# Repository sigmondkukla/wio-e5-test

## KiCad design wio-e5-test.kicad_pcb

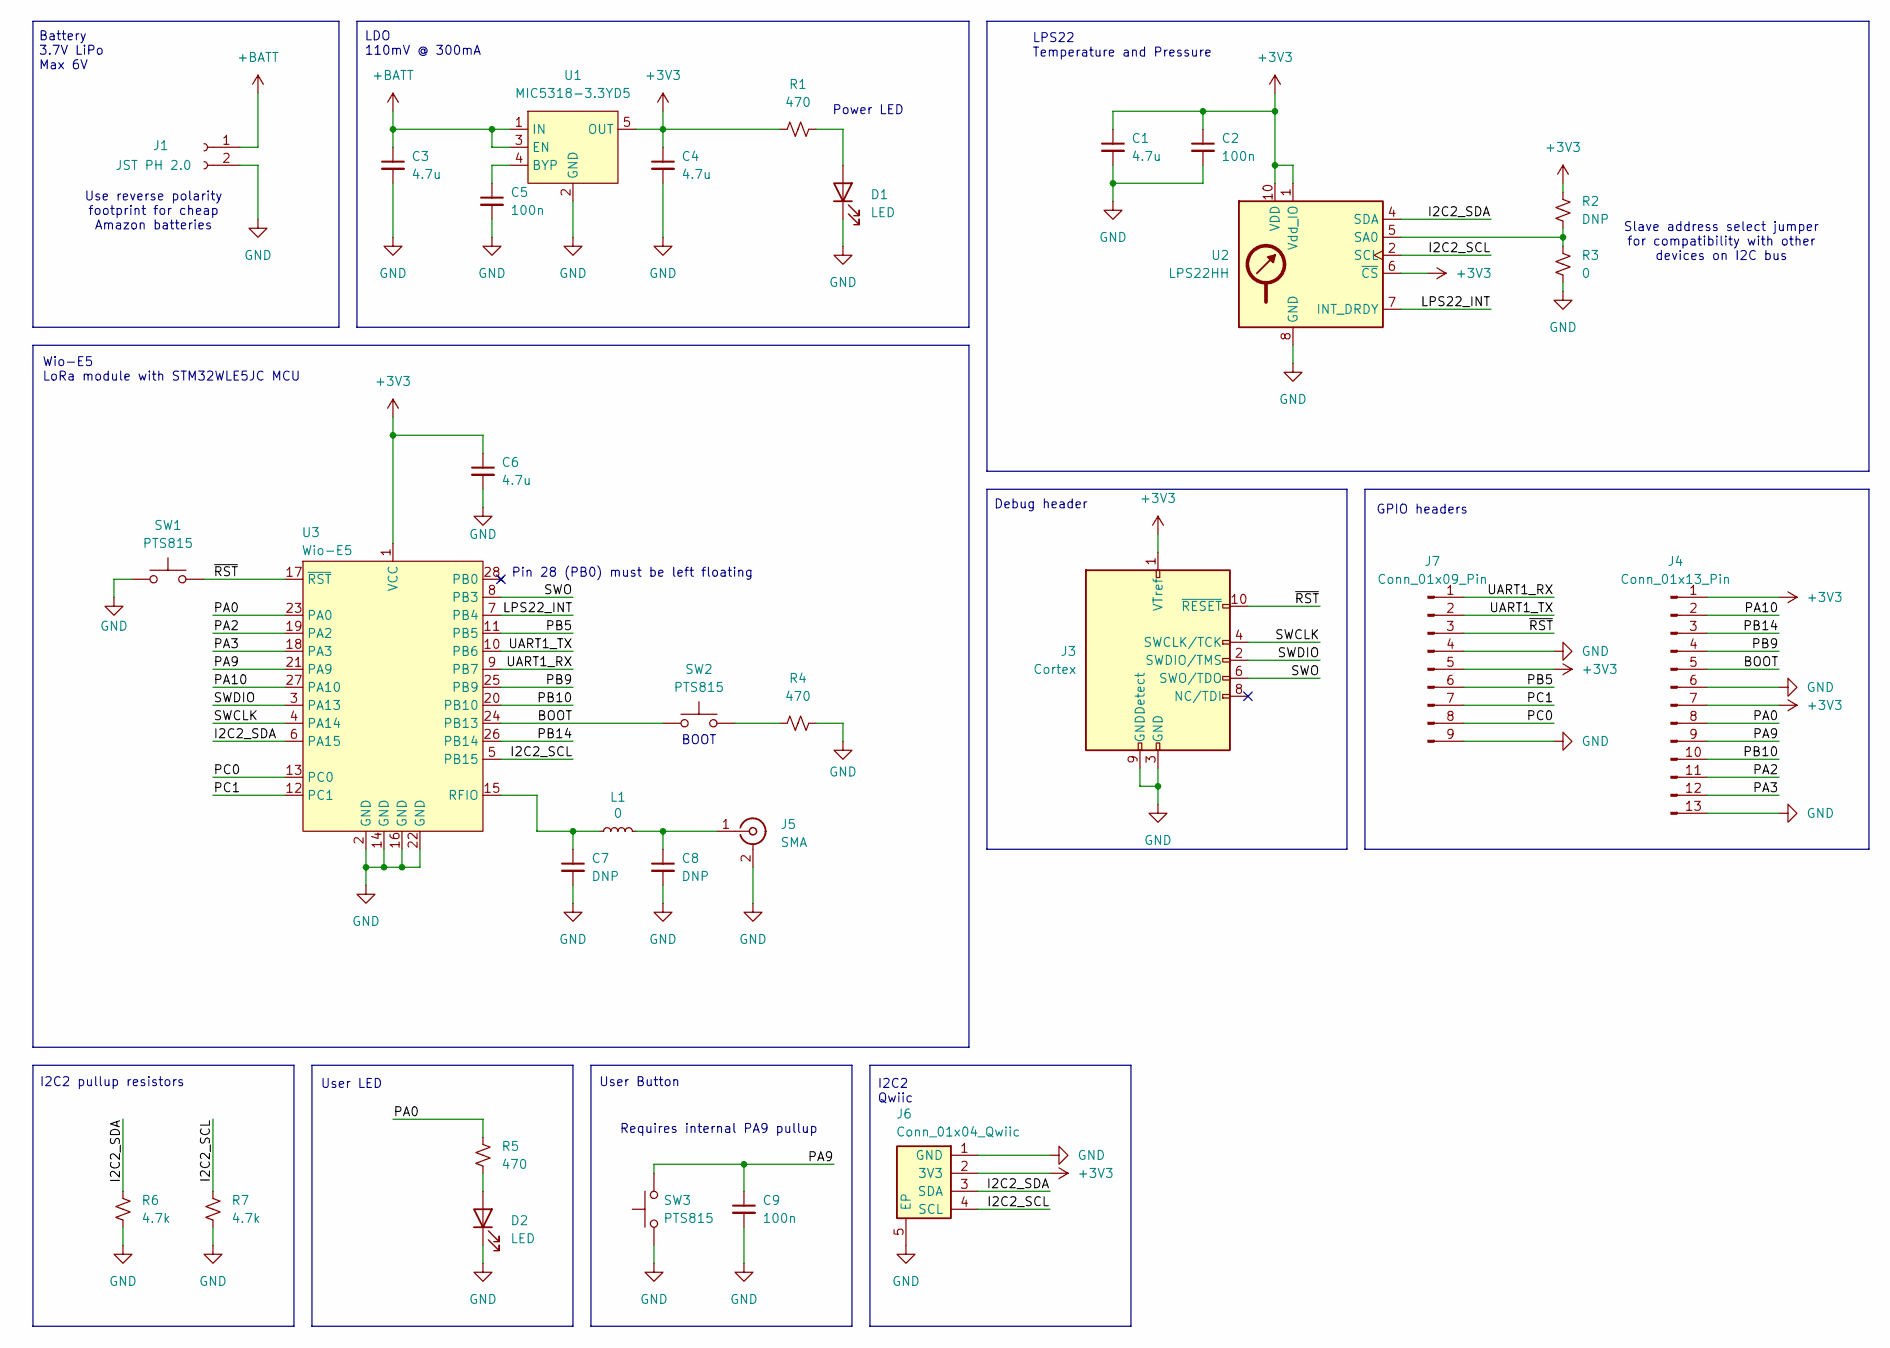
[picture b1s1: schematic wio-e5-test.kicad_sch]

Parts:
C1, C3, C4, C6: 4.7u; C_0603_1608Metric
C2, C5, C9: 100n; C_0603_1608Metric
C7, C8: DNP; C_0603_1608Metric
D1, D2: LED; LED_0603_1608Metric
J1: JST PH 2.0; JST_PH_S2B-PH-K_1x02_P2.00mm_Horizontal
J3: Cortex; CONN_3220-10-0100-00_CNC
J4: Conn_01x13_Pin; PinHeader_1x13_P2.54mm_Vertical
J5: SMA; SMA_Samtec_SMA-J-P-H-ST-EM1_EdgeMount
J6: Conn_01x04_Qwiic; CONN_JST-BM04B-SRSS-TB
J7: Conn_01x09_Pin; PinHeader_1x09_P2.54mm_Vertical
L1: 0; L_0603_1608Metric
R1, R4, R5: 470; R_0603_1608Metric
R2: DNP; R_0603_1608Metric
R3: 0; R_0603_1608Metric
R6, R7: 4.7k; R_0603_1608Metric
SW1, SW2, SW3: PTS815; SW_Push_PTS815_SJM_250_SMTR_LFS
U1: MIC5318-3.3YD5; SOT-23-5
U2: LPS22HH; ST_HLGA-10_2x2mm_P0.5mm_LayoutBorder3x2y
U3: Wio-E5

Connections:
+3V3: C1.1, C2.1, C4.1, C6.1, J3.1 (VTref), J4.1, J4.7, J6.2 (3V3), J7.5, R1.1, R2.1, U1.5 (OUT), U2.1 (Vdd_IO), U2.6 (~CS), U2.10 (VDD), U3.1 (VCC)
+BATT: C3.1, J1.1, U1.1 (IN), U1.3 (EN)
/BOOT: J4.5, SW2.1, U3.24 (PB13)
/I2C2_SCL: J6.4 (SCL), R7.1, U2.2 (SCL), U3.5 (PB15)
/I2C2_SDA: J6.3 (SDA), R6.1, U2.4 (SDA), U3.6 (PA15)
/LPS22_INT: U2.7 (INT_DRDY), U3.7 (PB4)
/PA0: J4.8, R5.1, U3.23 (PA0)
/PA2: J4.11, U3.19 (PA2)
/PA3: J4.12, U3.18 (PA3)
/PA9: C9.1, J4.9, SW3.2, U3.21 (PA9)
/PA10: J4.2, U3.27 (PA10)
/PB5: J7.6, U3.11 (PB5)
/PB9: J4.4, U3.25 (PB9)
/PB10: J4.10, U3.20 (PB10)
/PB14: J4.3, U3.26 (PB14)
/PC0: J7.8, U3.13 (PC0)
/PC1: J7.7, U3.12 (PC1)
/SWCLK: J3.4 (SWCLK/TCK), U3.4 (PA14)
/SWDIO: J3.2 (SWDIO/TMS), U3.3 (PA13)
/SWO: J3.6 (SWO/TDO), U3.8 (PB3)
/UART1_RX: J7.1, U3.9 (PB7)
/UART1_TX: J7.2, U3.10 (PB6)
/~RST: J3.10 (~RESET), J7.3, SW1.2, U3.17 (~RST)
GND: C1.2, C2.2, C3.2, C4.2, C5.2, C6.2, C7.2, C8.2, C9.2, D1.1 (K), D2.1 (K), J1.2, J3.3 (GND), J3.5 (GND), J3.9 (GNDDetect), J4.6, J4.13, J5.2 (Ext), J6.1 (GND), J6.5 (EP), J7.4, J7.9, R3.2, R4.2, R6.2, R7.2, SW1.1, SW3.1, U1.2 (GND), U2.3 (GND), U2.8 (GND), U2.9 (GND), U3.2 (GND), U3.14 (GND), U3.16 (GND), U3.22 (GND)
unnamed: D1.2 (A), R1.2
unnamed: D2.2 (A), R5.2
unnamed: C8.1, J5.1 (In), L1.2
unnamed: R4.1, SW2.2
unnamed: C5.1, U1.4 (BYP)
unnamed: R2.2, R3.1, U2.5 (SA0)
unnamed: C7.1, L1.1, U3.15 (RFIO)

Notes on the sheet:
LPS22 Temperature and Pressure
User Button
Slave address select jumper for compatibility with other devices on I2C bus
Wio-E5 LoRa module with STM32WLE5JC MCU
I2C2 pullup resistors
Battery 3.7V LiPo Max 6V
Power LED
I2C2 Qwiic
LDO 110mV @ 300mA
Pin 28 (PB0) must be left floating
BOOT
Requires internal PA9 pullup
Debug header
Use reverse polarity footprint for cheap Amazon batteries
GPIO headers
User LED

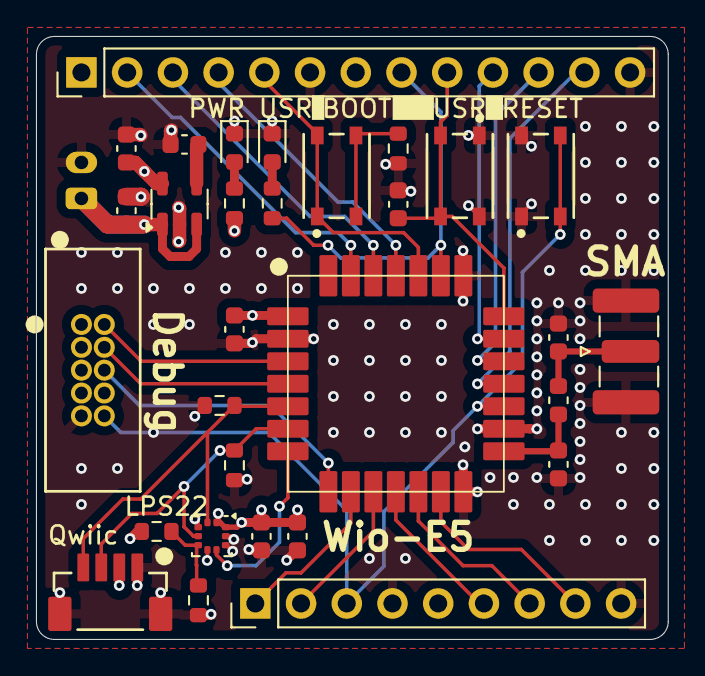
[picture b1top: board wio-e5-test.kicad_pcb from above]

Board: 4 copper layers, 35.1 x 33.5 mm, 31 parts (1 on the bottom side), 31 nets.

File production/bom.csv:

Designator,Footprint,Quantity,Value,LCSC Part #
"C1, C3, C4, C6",0603,4,4.7u,
"C2, C5, C9",0603,3,100n,
"C7, C8, R2",0603,3,DNP,
"D1, D2",0603,2,LED,
J1,JST_PH_S2B-PH-K_1x02_P2.00mm_Horizontal,1,JST PH 2.0,
J3,CONN_3220-10-0100-00_CNC,1,Cortex,
J4,PinHeader_1x13_P2.54mm_Vertical,1,Conn_01x13_Pin,
J5,SMA_Samtec_SMA-J-P-H-ST-EM1_EdgeMount,1,SMA,
J6,CONN_JST-BM04B-SRSS-TB,1,Conn_01x04_Qwiic,
J7,PinHeader_1x09_P2.54mm_Vertical,1,Conn_01x09_Pin,
"L1, R3",0603,2,0,
"R1, R4, R5",0603,3,470,
"R6, R7",0603,2,4.7k,
"SW1, SW2, SW3",SW_Push_PTS815_SJM_250_SMTR_LFS,3,PTS815,
U1,SOT-23-5,1,MIC5318-3.3YD5,
U2,ST_HLGA-10_2x2mm_P0.5mm_LayoutBorder3x2y,1,LPS22HH,
U3,Wio-E5,1,Wio-E5,

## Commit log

2025-07-01 Move schematic stuff around
